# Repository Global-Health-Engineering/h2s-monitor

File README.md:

# H2S Monitor

Design and Development of a Low-Cost Hydrogen Sulfide Sensor System for Biogas Monitoring

**Author:** Flurin Vital
**Supervisors:** Prof. Dr. Elizabeth Tilley, Dr. Jakub Tkaczuk
**Institution:** ETH Zürich, Global Health Engineering (GHE)
**Date:** June 2026

## Overview

This project develops a low-cost, field-deployable hydrogen sulfide (H2S) sensor system for monitoring biogas quality. Biogas systems in low-resource settings frequently lack affordable tools for measuring H2S — a toxic and corrosive gas produced during anaerobic digestion that causes equipment degradation and safety hazards. Commercial H2S meters capable of covering the relevant concentration range (0–2000 ppm) cost upwards of CHF 4000 and are unsuitable for continuous field deployment.

The developed system integrates a three-electrode electrochemical H2S sensor into a single compact battery-powered device with a custom PCB, 3D-printed enclosure and gas flow chamber, and C++ firmware running on FreeRTOS. Total component cost is CHF 193.80 — approximately 95% cheaper than the commercial reference instrument (Dräger X-am 8000).

## System Components

| Component | Part |
|---|---|
| Microcontroller | Seeed XIAO ESP32-C6 |
| H2S Sensor | SUCH electrochemical, 0–2000 ppm, 85 ± 25 nA/ppm |
| Analog Front End | Texas Instruments LMP91002 |
| ADC | Texas Instruments ADS1115 (16-bit) |
| Display | 0.96" OLED, SSD1306 driver |
| RTC | Maxim DS3232M |
| Power Management | Texas Instruments BQ25185 |
| Storage | MicroSD card (SPI) |
| Gas Pump | DC micro diaphragm pump, 1.2 L/min |
| PCB | KiCad design, manufactured by JLCPCB |
| Enclosure | 3D-printed PLA (case) + resin (flow chamber) |

## Repository Structure

```
├── analysis/
├── data/
├── docs/
├── grading/
├── hardware/
├── media/
└── src/
```

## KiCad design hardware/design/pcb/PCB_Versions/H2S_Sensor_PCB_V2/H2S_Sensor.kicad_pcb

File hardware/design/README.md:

# Design

PCB schematic and layout files, and CAD models for the enclosure and gas flow chamber.

## Structure

```
design/
├── pcb/
└── case_CAD/
```

## PCB (`pcb/`)

Designed in KiCad. The schematic is organised into functional blocks:
- **Power management** — TI BQ25185 (USB-C charging, single-cell LiPo, power path)
- **Microcontroller** — Seeed XIAO ESP32-C6
- **Analog front end & ADC** — TI LMP91002 + TI ADS1115 for electrochemical sensor signal conditioning
- **Peripherals** — DS3232M RTC, SSD1306 OLED, MicroSD (SPI), pump MOSFET driver

Production files in `pcb/production/` and `pcb/jlcpcb/` were submitted to JLCPCB for fabrication and assembly. `pcb/PCB_Versions/` contains archived snapshots of earlier design iterations (V1–V5).

The electrochemical sensor uses a custom KiCad footprint with press-fit through-hole pads — the sensor cannot withstand soldering temperatures and must not be soldered.

## CAD (`case_CAD/`)

Designed in OnShape, exported as STL for 3D printing.

| File | Material | Notes |
|---|---|---|
| `Case/Final/Case_Bottom.stl` | PLA | Houses PCB |
| `Case/Final/Case_Top.stl` | PLA | Carries OLED display |
| `Flow_Chamber/Flow_Chamber_final.stl` | Resin (field) / PLA (bench test) | Seals around sensor body with O-ring |

`Case/V1`–`V5` and `Flow_Chamber/V1`–`V5` contain earlier design iterations.

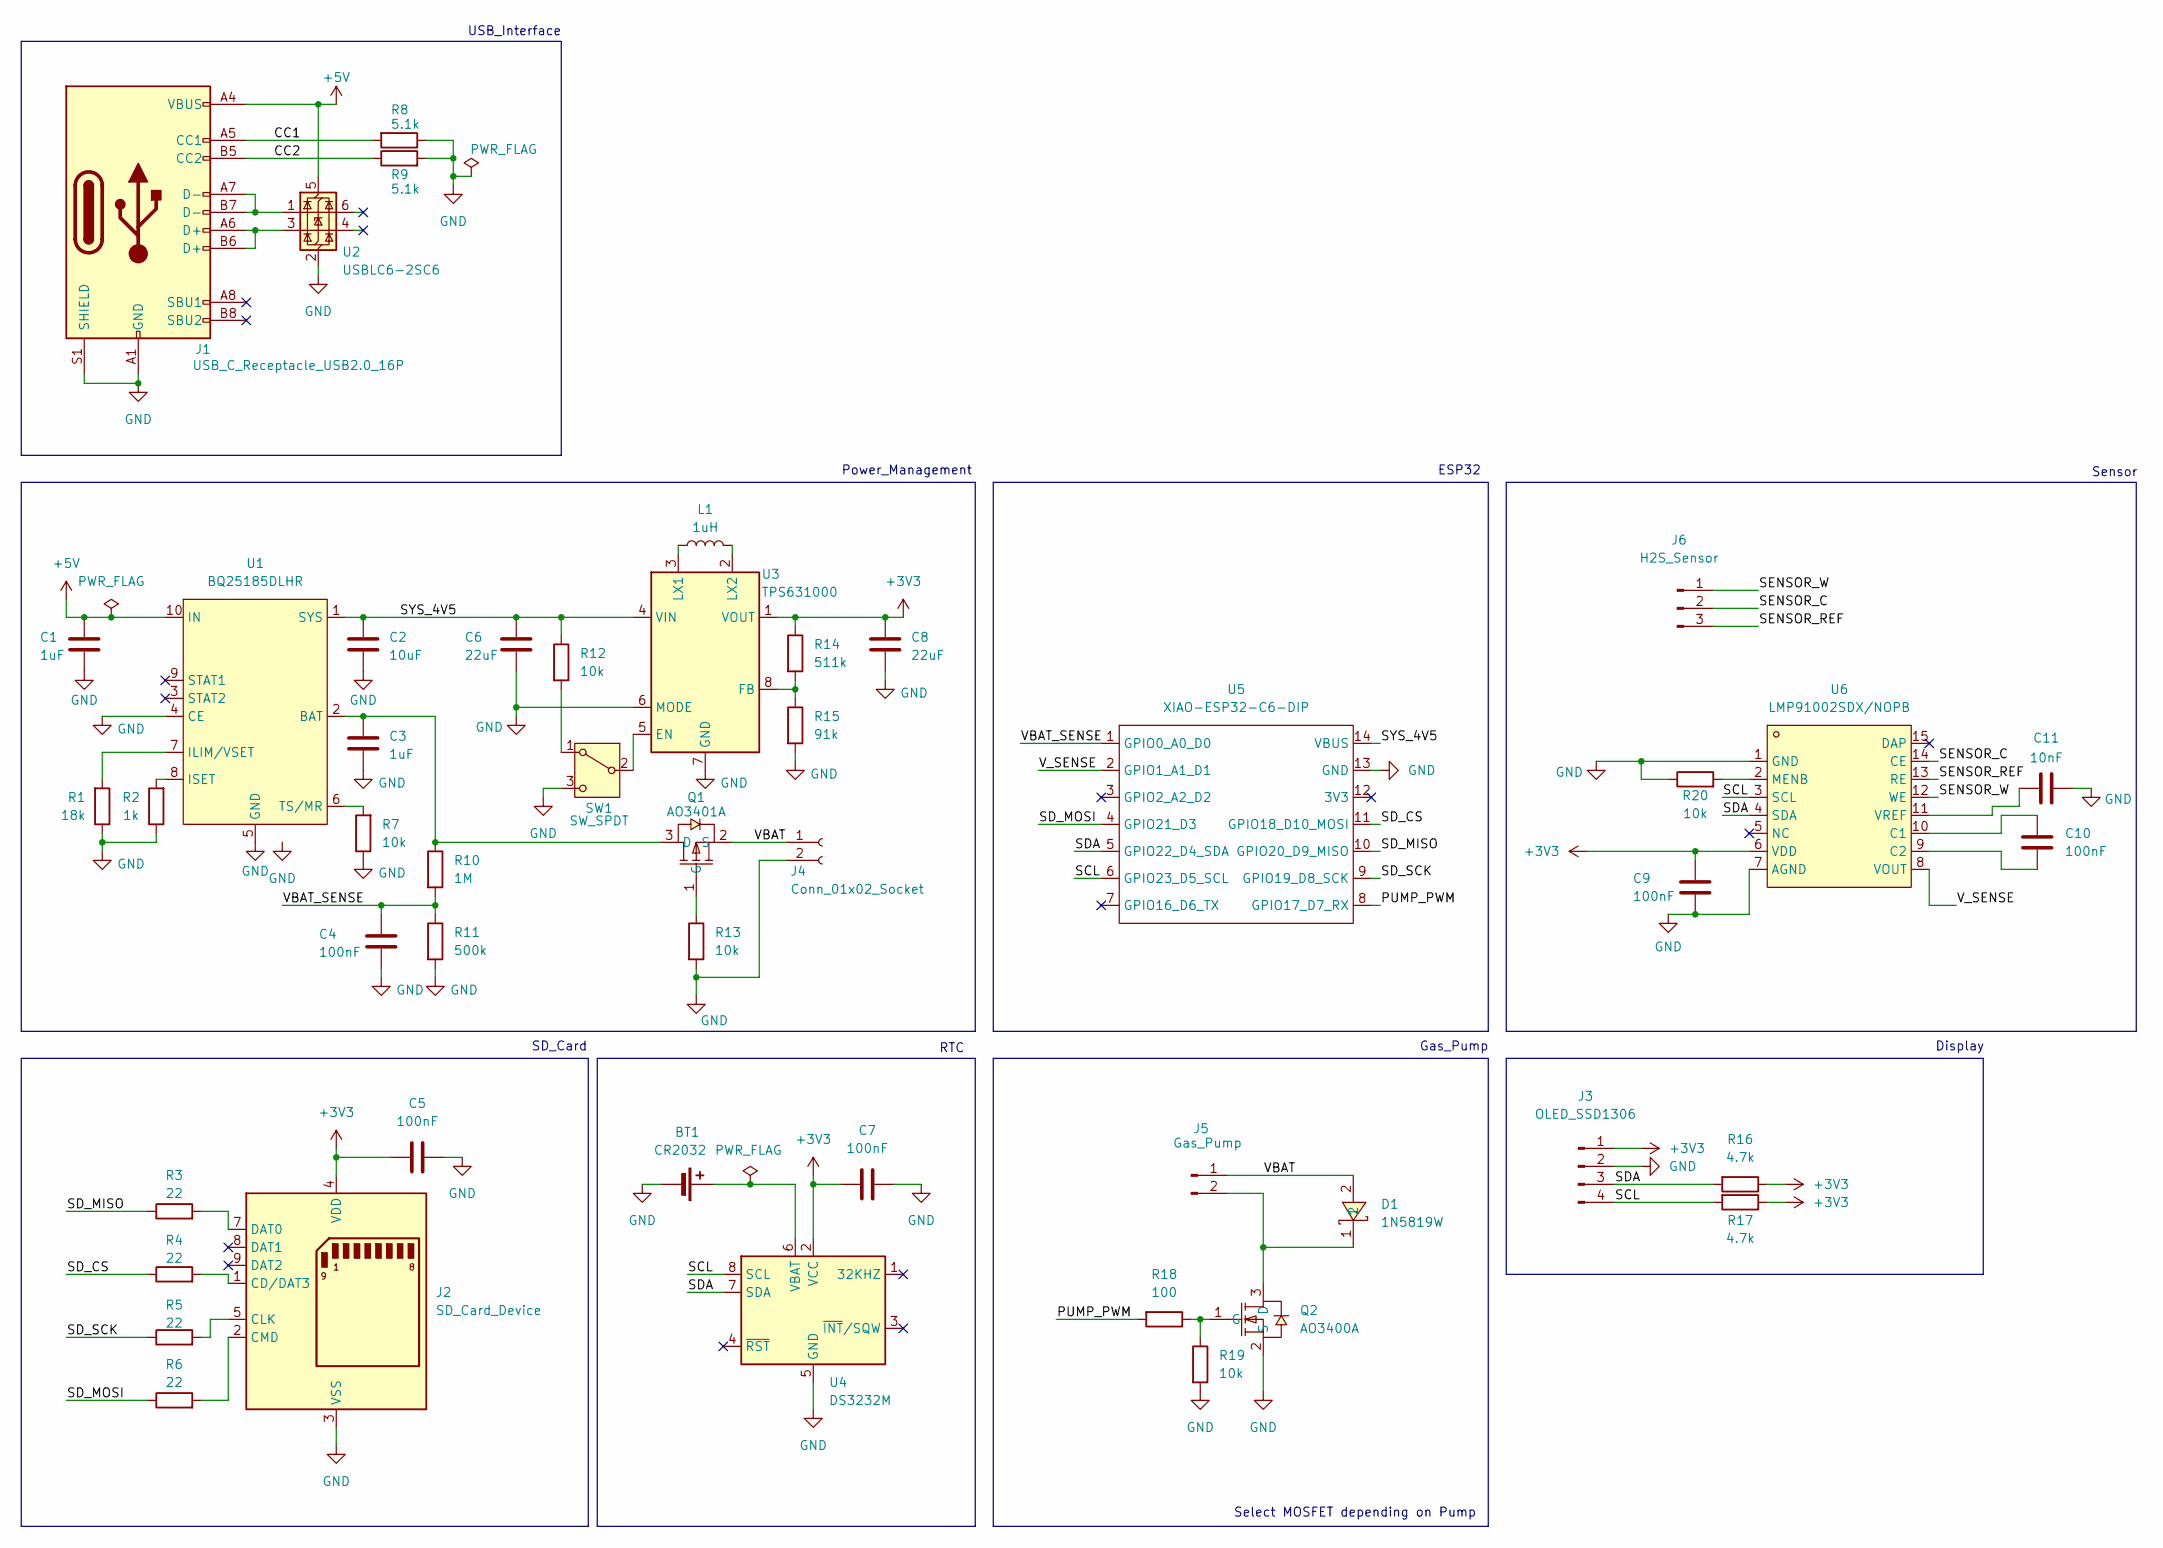
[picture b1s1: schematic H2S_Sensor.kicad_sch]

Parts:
BT1: CR2032; BAT-TH_CR2032-BS-6-1; LCSC Part C70377
C1, C3: 1uF; C_0603_1608Metric
C2: 10uF; C_0603_1608Metric
C4, C5, C7, C9, C10: 100nF; C_0603_1608Metric
C6, C8: 22uF; C_0603_1608Metric
C11: 10nF; C_0603_1608Metric
D1: 1N5819W; SOD-123F_L2.8-W1.8-LS3.7-RD; MPN 1N5819W; LCSC Part C169540
J1: USB_C_Receptacle_USB2.0_16P; USB_C_Receptacle_GCT_USB4105-xx-A_16P_TopMnt_Horizontal
J2: SD_Card_Device; SD-SMD_5045280892; LCSC Part C125620
J3: OLED_SSD1306; Hirose_DF13-04P-1.25DSA_1x04_P1.25mm_Vertical
J4: Conn_01x02_Socket; Hirose_DF13-02P-1.25DSA_1x02_P1.25mm_Vertical
J5: Gas_Pump; Hirose_DF13-02P-1.25DSA_1x02_P1.25mm_Vertical
J6: H2S_Sensor; H2S_Sensor_3Pin_D20mm
L1: 1uH; L_0805_2012Metric
Q1: AO3401A; SOT-23_L2.9-W1.3-P1.90-LS2.4-BR; MPN AO3401A; LCSC Part C15127
Q2: AO3400A; SOT-23-3_L2.9-W1.3-P1.90-LS2.4-BR; MPN AO3400A; LCSC Part C20917
R1: 18k; R_0603_1608Metric
R2: 1k; R_0603_1608Metric
R3, R4, R5, R6: 22; R_0603_1608Metric
R7, R12, R13, R19, R20: 10k; R_0603_1608Metric
R8, R9: 5.1k; R_0603_1608Metric
R10: 1M; R_0603_1608Metric
R11: 500k; R_0603_1608Metric
R14: 511k; R_0603_1608Metric
R15: 91k; R_0603_1608Metric
R16, R17: 4.7k; R_0603_1608Metric
R18: 100; R_0603_1608Metric
SW1: SW_SPDT; SW-SMD_MSK-03-HB; LCSC Part C54948
U1: BQ25185DLHR; WSON-10_L2.2-W2.0-P0.40-BL-EP_TI_DLH0010A; LCSC Part C19725033
U2: USBLC6-2SC6; SOT-23-6_L2.9-W1.6-P0.95-LS2.8-BL; LCSC Part C7519
U3: TPS631000; SOT-583-8_L2.1-W1.2-P0.50-LS1.6-BL; LCSC Part C5219190
U4: DS3232M; SOIC-8_3.9x4.9mm_P1.27mm
U5: XIAO-ESP32-C6-DIP
U6: LMP91002SDX/NOPB; WSON-14_L4.0-W4.0-P0.50-BL-EP; MPN LMP91002SDX/NOPB; LCSC Part C2651581

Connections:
+3V3: C5.1, C7.2, C8.2, C9.1, J2.4 (VDD), J3.1, R14.1, R16.1, R17.1, U3.1 (VOUT), U4.2 (VCC), U6.6 (VDD)
+5V: C1.2, J1.A4 (VBUS), J1.A9 (VBUS), J1.B4 (VBUS), J1.B9 (VBUS), U1.10 (IN), U2.5 (VBUS)
/CC1: J1.A5 (CC1), R8.2
/CC2: J1.B5 (CC2), R9.1
/PUMP_PWM: R18.2, U5.8 (GPIO17_D7_RX)
/SCL: J3.4, R17.2, U4.8 (SCL), U5.6 (GPIO23_D5_SCL), U6.3 (SCL)
/SDA: J3.3, R16.2, U4.7 (SDA), U5.5 (GPIO22_D4_SDA), U6.4 (SDA)
/SD_CS: R4.1, U5.11 (GPIO18_D10_MOSI)
/SD_MISO: R3.1, U5.10 (GPIO20_D9_MISO)
/SD_MOSI: R6.1, U5.4 (GPIO21_D3)
/SD_SCK: R5.1, U5.9 (GPIO19_D8_SCK)
/SENSOR_C: J6.2, U6.14 (CE)
/SENSOR_REF: J6.3, U6.13 (RE)
/SENSOR_W: J6.1, U6.12 (WE)
/SYS_4V5: C2.2, C6.2, R12.1, U1.1 (SYS), U3.4 (VIN), U5.14 (VBUS)
/VBAT: D1.2, J4.1, J5.1, Q1.2 (S)
/VBAT_SENSE: C4.1, R10.2, R11.1, U5.1 (GPIO0_A0_D0)
/V_SENSE: U5.2 (GPIO1_A1_D1), U6.8 (VOUT)
GND: BT1.2 (-), C1.1, C2.1, C3.1, C4.2, C5.2, C6.1, C7.1, C8.1, C9.2, C11.2, J1.A1 (GND), J1.A12 (GND), J1.B1 (GND), J1.B12 (GND), J1.S1 (SHIELD), J2.3 (VSS), J2.6 (VSS), J3.2, J4.2, Q2.2 (S), R1.1, R2.1, R7.1, R8.1, R9.2, R11.2, R13.2, R15.2, R19.2, R20.1, SW1.3 (C), U1.4 (CE), U1.5 (GND), U1.11 (VSS), U2.2 (GND), U3.6 (MODE), U3.7 (GND), U4.5 (GND), U5.13 (GND), U6.1 (GND), U6.7 (AGND), U6.15 (DAP)
unnamed: BT1.1 (+), U4.6 (VBAT)
unnamed: J1.A6 (D+), J1.B6 (D+), U2.3 (I/O2)
unnamed: J1.A7 (D-), J1.B7 (D-), U2.1 (I/O1)
unnamed: J2.1 (CD/DAT3), R4.2
unnamed: J2.5 (CLK), R5.2
unnamed: J2.2 (CMD), R6.2
unnamed: J2.7 (DAT0), R3.2
unnamed: D1.1, J5.2, Q2.3 (D)
unnamed: C3.2, Q1.3 (D), R10.1, U1.2 (BAT)
unnamed: Q1.1 (G), R13.1
unnamed: Q2.1 (G), R18.1, R19.1
unnamed: R12.2, SW1.1 (A)
unnamed: SW1.2 (B), U3.5 (EN)
unnamed: R1.2, U1.7 (ILIM/VSET)
unnamed: R2.2, U1.8 (ISET)
unnamed: R7.2, U1.6 (TS/MR)
unnamed: R14.2, R15.1, U3.8 (FB)
unnamed: L1.1, U3.3 (LX1)
unnamed: L1.2, U3.2 (LX2)
unnamed: C10.1, U6.10 (C1)
unnamed: C10.2, U6.9 (C2)
unnamed: R20.2, U6.2 (MENB)
unnamed: C11.1, U6.11 (VREF)

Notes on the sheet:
Gas_Pump
Sensor
USB_Interface
ESP32
Display
RTC
Select MOSFET depending on Pump
SD_Card
Power_Management

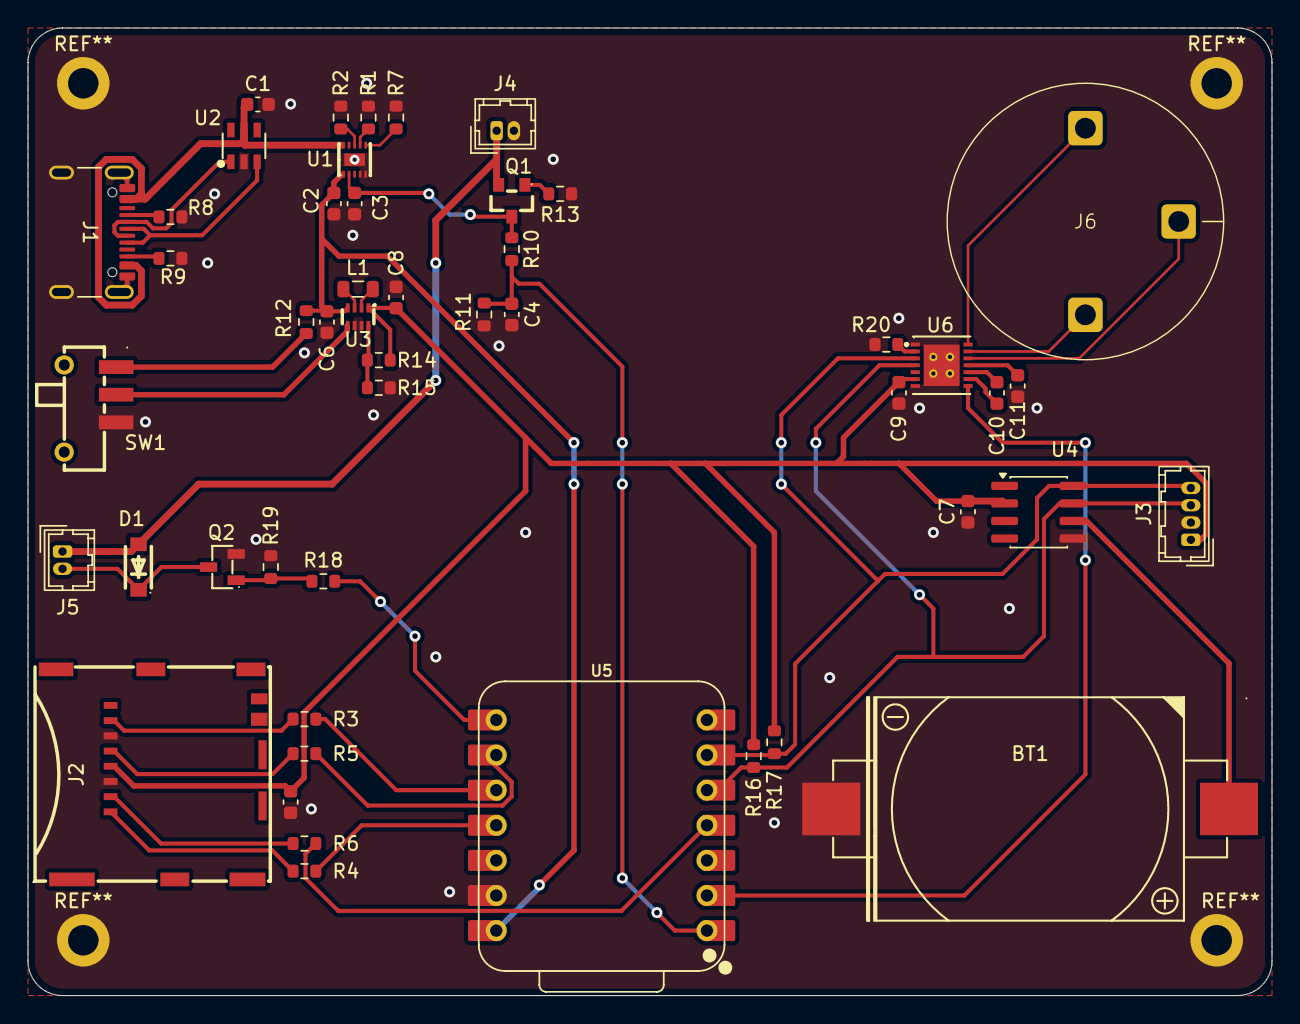
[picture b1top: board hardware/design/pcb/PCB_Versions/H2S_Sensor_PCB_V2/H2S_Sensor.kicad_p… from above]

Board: 2 copper layers, 90.0 x 70.0 mm, 49 parts (0 on the bottom side), 42 nets.

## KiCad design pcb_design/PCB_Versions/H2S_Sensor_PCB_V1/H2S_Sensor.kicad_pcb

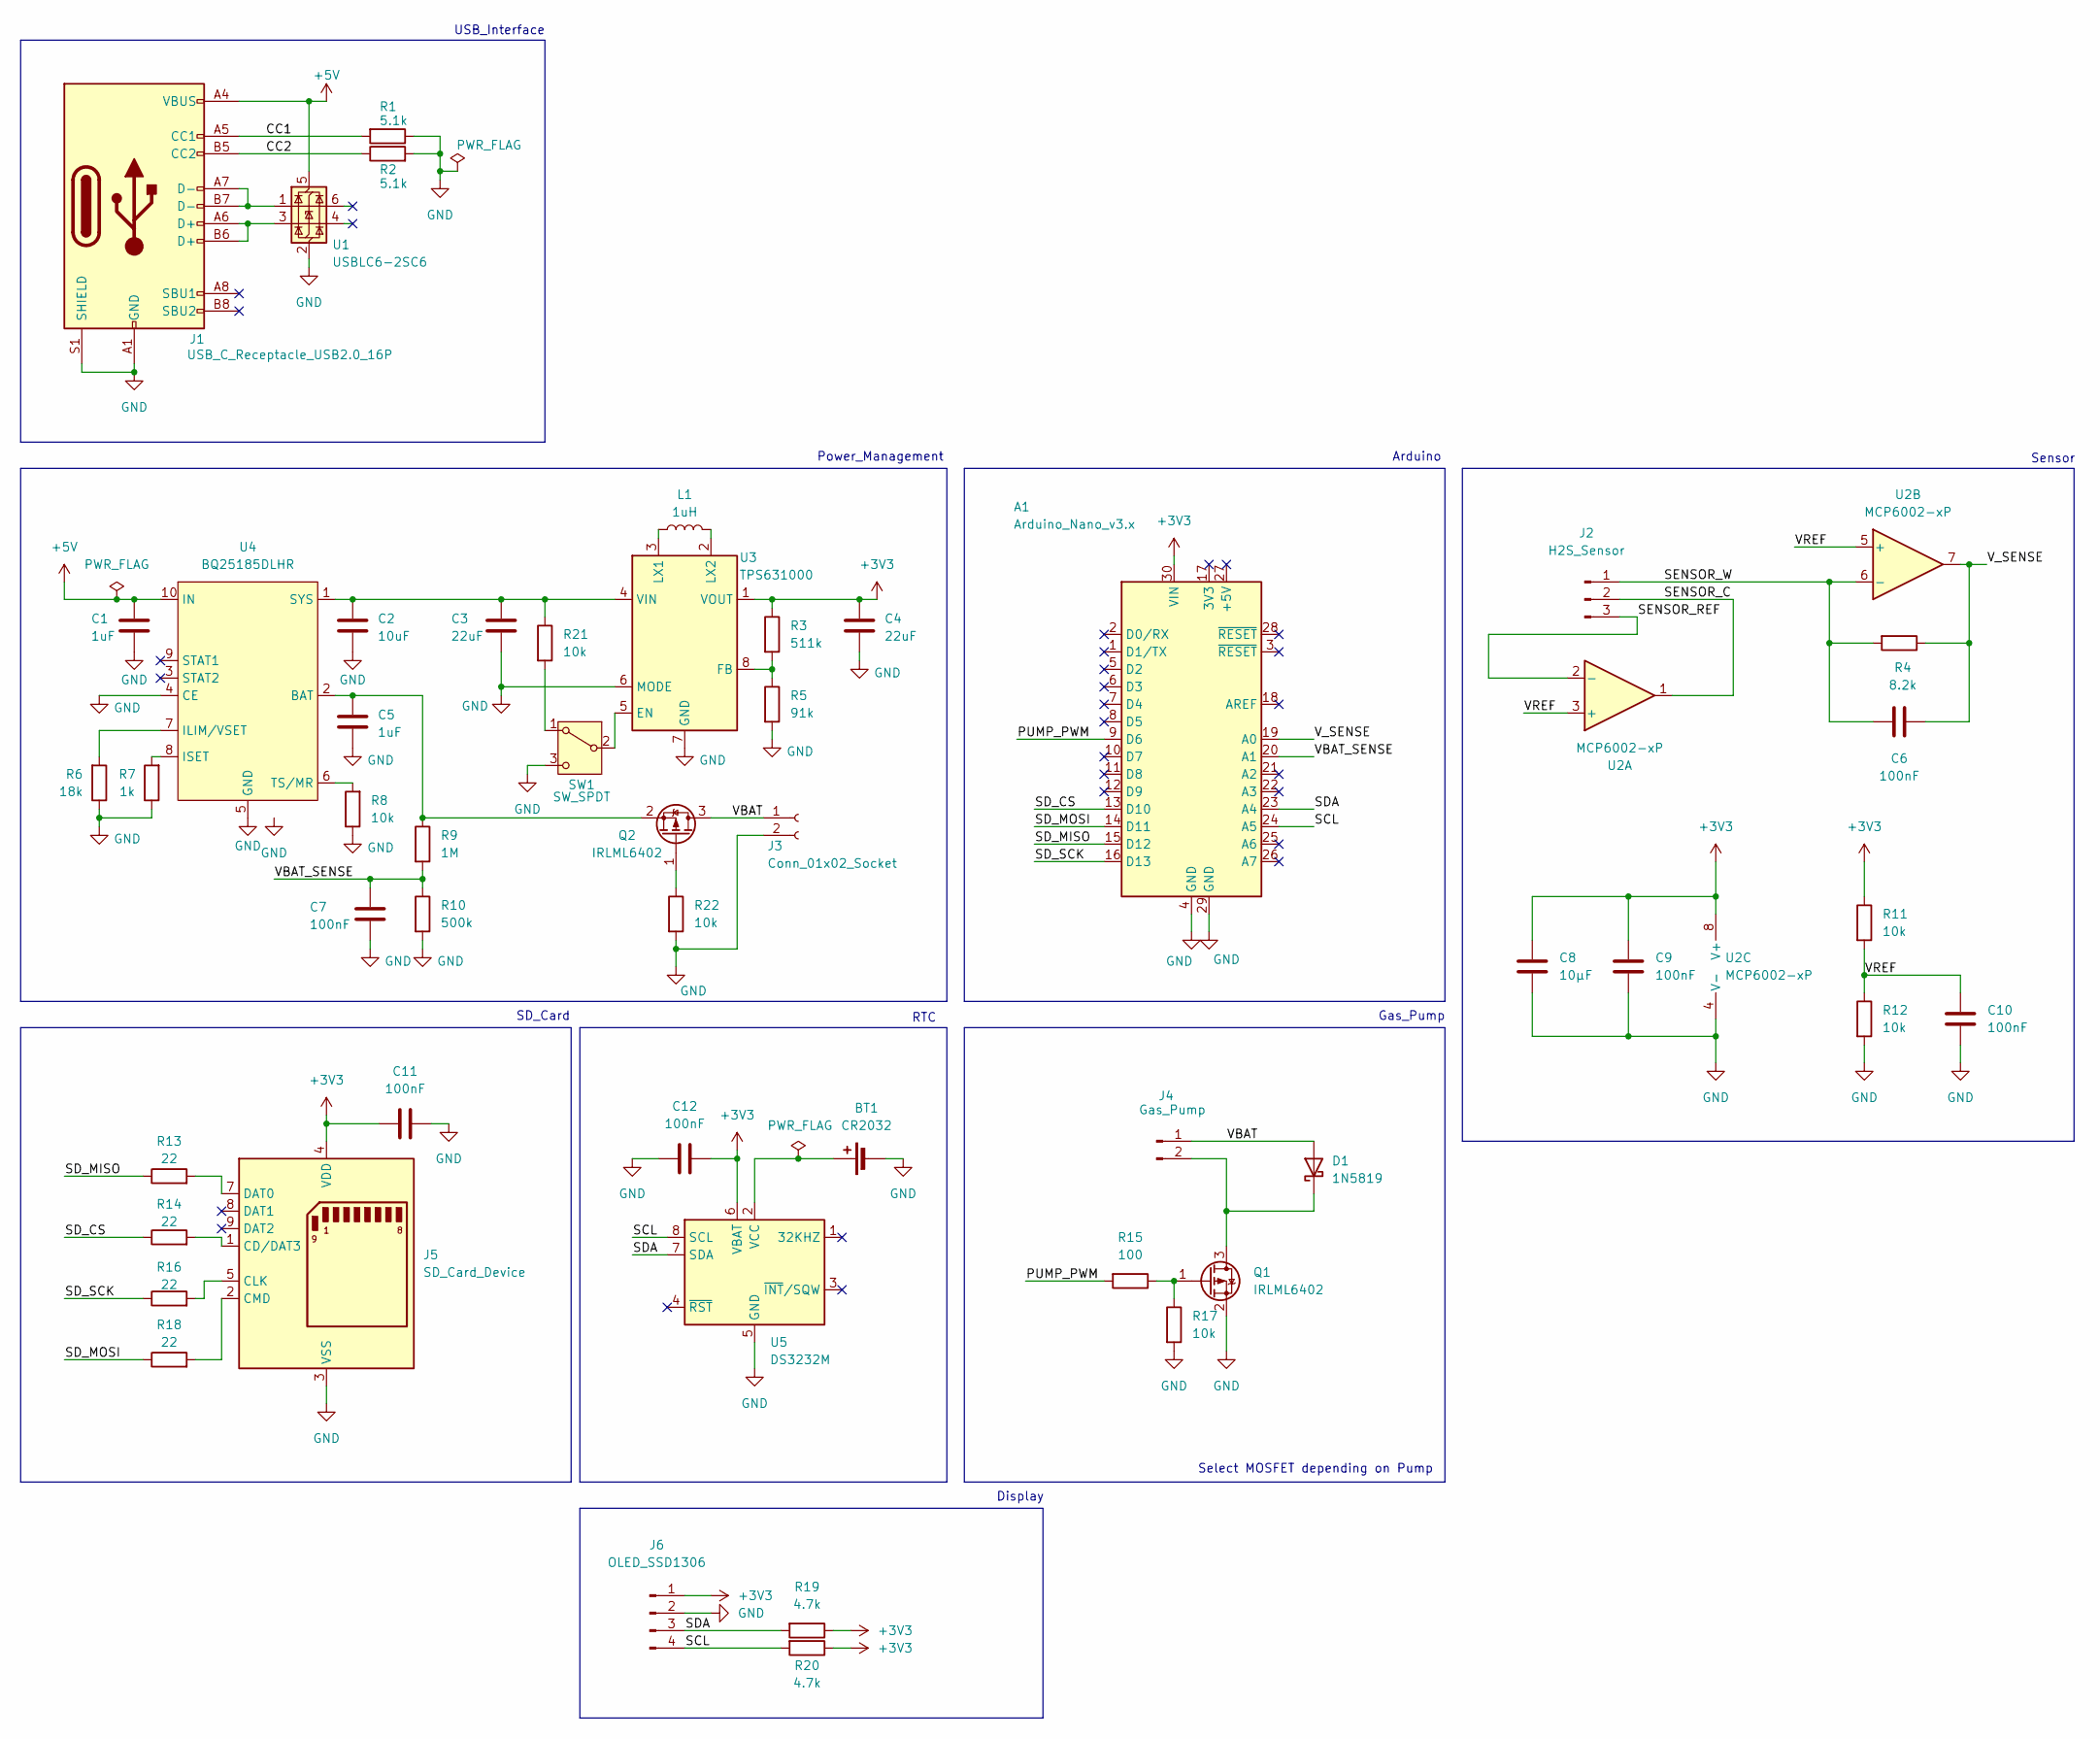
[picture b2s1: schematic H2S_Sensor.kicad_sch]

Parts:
A1: Arduino_Nano_v3.x; Arduino_Nano
BT1: CR2032; BAT-TH_CR2032-BS-6-1; LCSC Part C70377
C1, C5: 1uF; C_0603_1608Metric
C2: 10uF; C_0603_1608Metric
C3, C4: 22uF; C_0603_1608Metric
C6, C7, C9, C10, C11, C12: 100nF; C_0603_1608Metric
C8: 10µF; C_0603_1608Metric
D1: 1N5819; DO-41_BD2.4-L4.7-P8.70-D0.9-FD; LCSC Part C2474
J1: USB_C_Receptacle_USB2.0_16P; USB_C_Receptacle_GCT_USB4105-xx-A_16P_TopMnt_Horizontal
J2: H2S_Sensor; H2S_Sensor_3Pin_D20mm
J3: Conn_01x02_Socket; Hirose_DF13-02P-1.25DSA_1x02_P1.25mm_Vertical
J4: Gas_Pump; Hirose_DF13-02P-1.25DSA_1x02_P1.25mm_Vertical
J5: SD_Card_Device; SD-SMD_SD-006S-T; LCSC Part C125620
J6: OLED_SSD1306; Hirose_DF13-04P-1.25DSA_1x04_P1.25mm_Vertical
L1: 1uH; L_0805_2012Metric
Q1, Q2: IRLML6402; SOT-23
R1, R2: 5.1k; R_0603_1608Metric
R3: 511k; R_0603_1608Metric
R4: 8.2k; R_0603_1608Metric
R5: 91k; R_0603_1608Metric
R6: 18k; R_0603_1608Metric
R7: 1k; R_0603_1608Metric
R8, R11, R12, R17, R21, R22: 10k; R_0603_1608Metric
R9: 1M; R_0603_1608Metric
R10: 500k; R_0603_1608Metric
R13, R14, R16, R18: 22; R_0603_1608Metric
R15: 100; R_0603_1608Metric
R19, R20: 4.7k; R_0603_1608Metric
SW1: SW_SPDT; SW-SMD_MSK-03-HB; LCSC Part C54948
U1: USBLC6-2SC6; SOT-23-6_L2.9-W1.6-P0.95-LS2.8-BL; LCSC Part C7519
U2: MCP6002-xP; SOIC-8_3.9x4.9mm_P1.27mm
U3: TPS631000; SOT-583-8_L2.1-W1.2-P0.50-LS1.6-BL; LCSC Part C5219190
U4: BQ25185DLHR; WSON-10_L2.2-W2.0-P0.40-BL-EP_TI_DLH0010A; LCSC Part C19725033
U5: DS3232M; SOIC-8_3.9x4.9mm_P1.27mm

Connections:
+3V3: A1.30 (VIN), C4.2, C8.1, C9.1, C11.1, C12.2, J5.4 (VDD), J6.1, R3.1, R11.1, R19.1, R20.1, U2.8 (V+), U3.1 (VOUT), U5.6 (VBAT)
+5V: C1.2, J1.A4 (VBUS), J1.A9 (VBUS), J1.B4 (VBUS), J1.B9 (VBUS), U1.5 (VBUS), U4.10 (IN)
/CC1: J1.A5 (CC1), R1.2
/CC2: J1.B5 (CC2), R2.1
/PUMP_PWM: A1.9 (D6), R15.2
/SCL: A1.24 (A5), J6.4, R20.2, U5.8 (SCL)
/SDA: A1.23 (A4), J6.3, R19.2, U5.7 (SDA)
/SD_CS: A1.13 (D10), R14.1
/SD_MISO: A1.15 (D12), R13.1
/SD_MOSI: A1.14 (D11), R18.1
/SD_SCK: A1.16 (D13), R16.1
/SENSOR_C: J2.2, U2.1
/SENSOR_REF: J2.3, U2.2 (-)
/SENSOR_W: C6.1, J2.1, R4.2, U2.6 (-)
/VBAT: D1.2 (A), J3.1, J4.1, Q2.3 (D)
/VBAT_SENSE: A1.20 (A1), C7.1, R9.2, R10.1
/VREF: C10.1, R11.2, R12.1, U2.3 (+), U2.5 (+)
/V_SENSE: A1.19 (A0), C6.2, R4.1, U2.7
GND: A1.4 (GND), A1.29 (GND), BT1.2 (-), C1.1, C2.1, C3.1, C4.1, C5.1, C7.2, C8.2, C9.2, C10.2, C11.2, C12.1, J1.A1 (GND), J1.A12 (GND), J1.B1 (GND), J1.B12 (GND), J1.S1 (SHIELD), J3.2, J5.3 (VSS), J5.6 (VSS), J6.2, Q1.2 (S), R1.1, R2.2, R5.2, R6.1, R7.1, R8.1, R10.2, R12.2, R17.2, R22.2, SW1.3 (C), U1.2 (GND), U2.4 (V-), U3.6 (MODE), U3.7 (GND), U4.4 (CE), U4.5 (GND), U4.11 (VSS), U5.5 (GND)
unnamed: BT1.1 (+), U5.2 (VCC)
unnamed: D1.1 (K), J4.2, Q1.3 (D)
unnamed: J1.A6 (D+), J1.B6 (D+), U1.3 (I/O2)
unnamed: J1.A7 (D-), J1.B7 (D-), U1.1 (I/O1)
unnamed: J5.1 (CD/DAT3), R14.2
unnamed: J5.5 (CLK), R16.2
unnamed: J5.2 (CMD), R18.2
unnamed: J5.7 (DAT0), R13.2
unnamed: Q1.1 (G), R15.1, R17.1
unnamed: Q2.1 (G), R22.1
unnamed: C5.2, Q2.2 (S), R9.1, U4.2 (BAT)
unnamed: R21.2, SW1.1 (A)
unnamed: SW1.2 (B), U3.5 (EN)
unnamed: R3.2, R5.1, U3.8 (FB)
unnamed: L1.1, U3.3 (LX1)
unnamed: L1.2, U3.2 (LX2)
unnamed: C2.2, C3.2, R21.1, U3.4 (VIN), U4.1 (SYS)
unnamed: R6.2, U4.7 (ILIM/VSET)
unnamed: R7.2, U4.8 (ISET)
unnamed: R8.2, U4.6 (TS/MR)

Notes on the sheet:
Gas_Pump
Sensor
USB_Interface
Arduino
Display
RTC
Select MOSFET depending on Pump
SD_Card
Power_Management

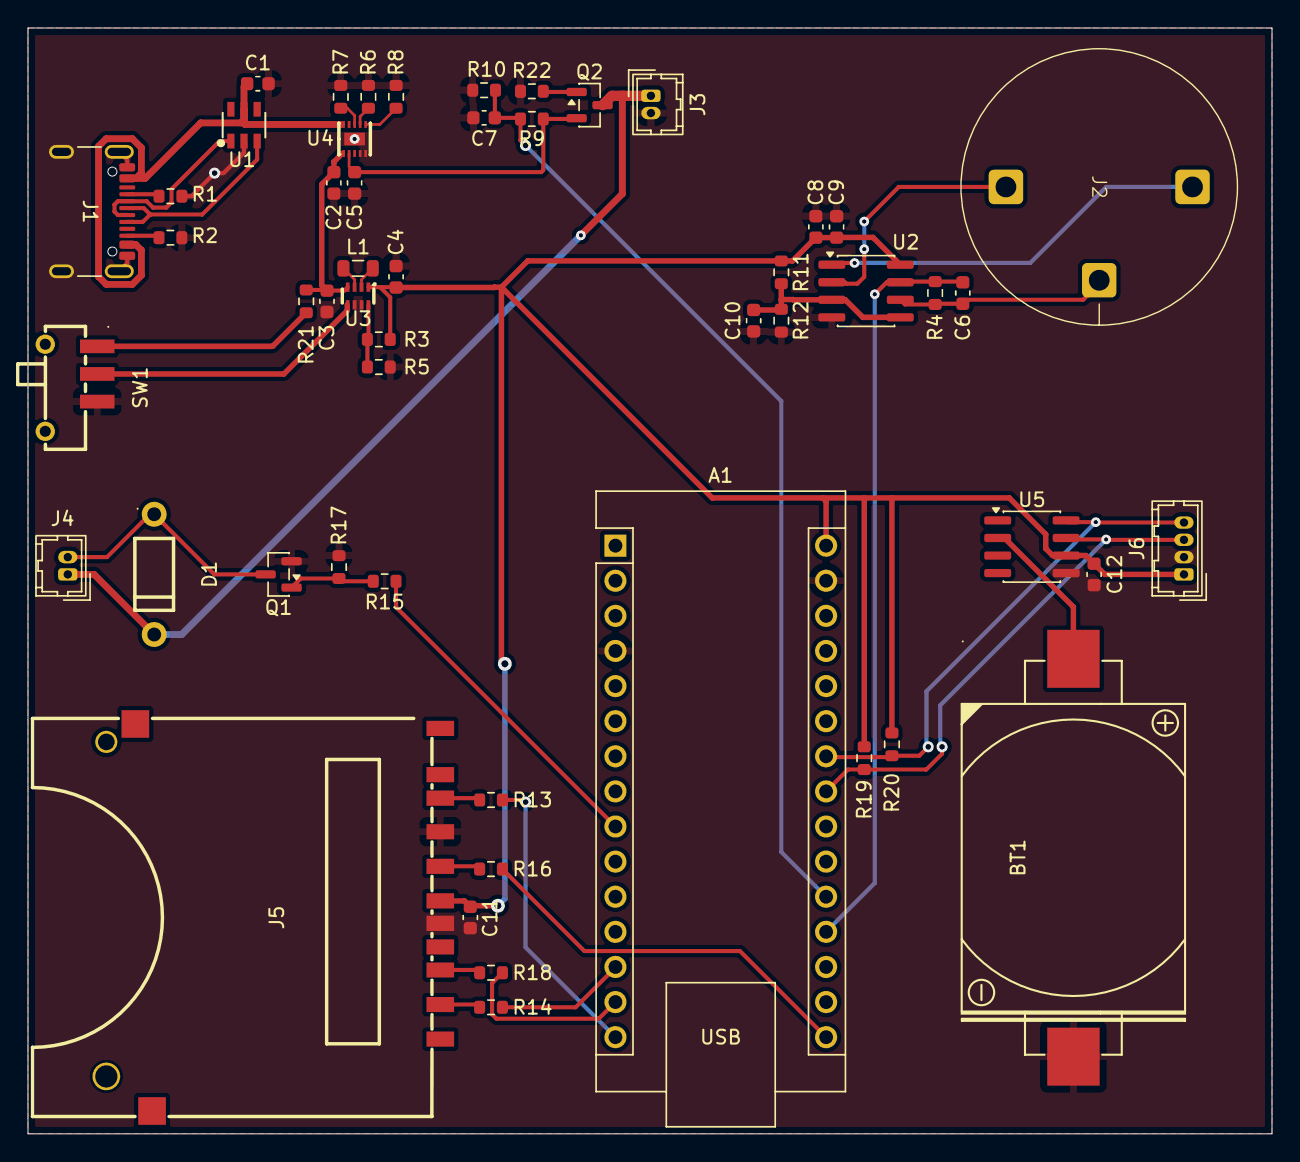
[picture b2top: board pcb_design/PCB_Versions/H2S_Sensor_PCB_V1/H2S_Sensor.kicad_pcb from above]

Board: 2 copper layers, 90.0 x 80.0 mm, 52 parts (0 on the bottom side), 39 nets.

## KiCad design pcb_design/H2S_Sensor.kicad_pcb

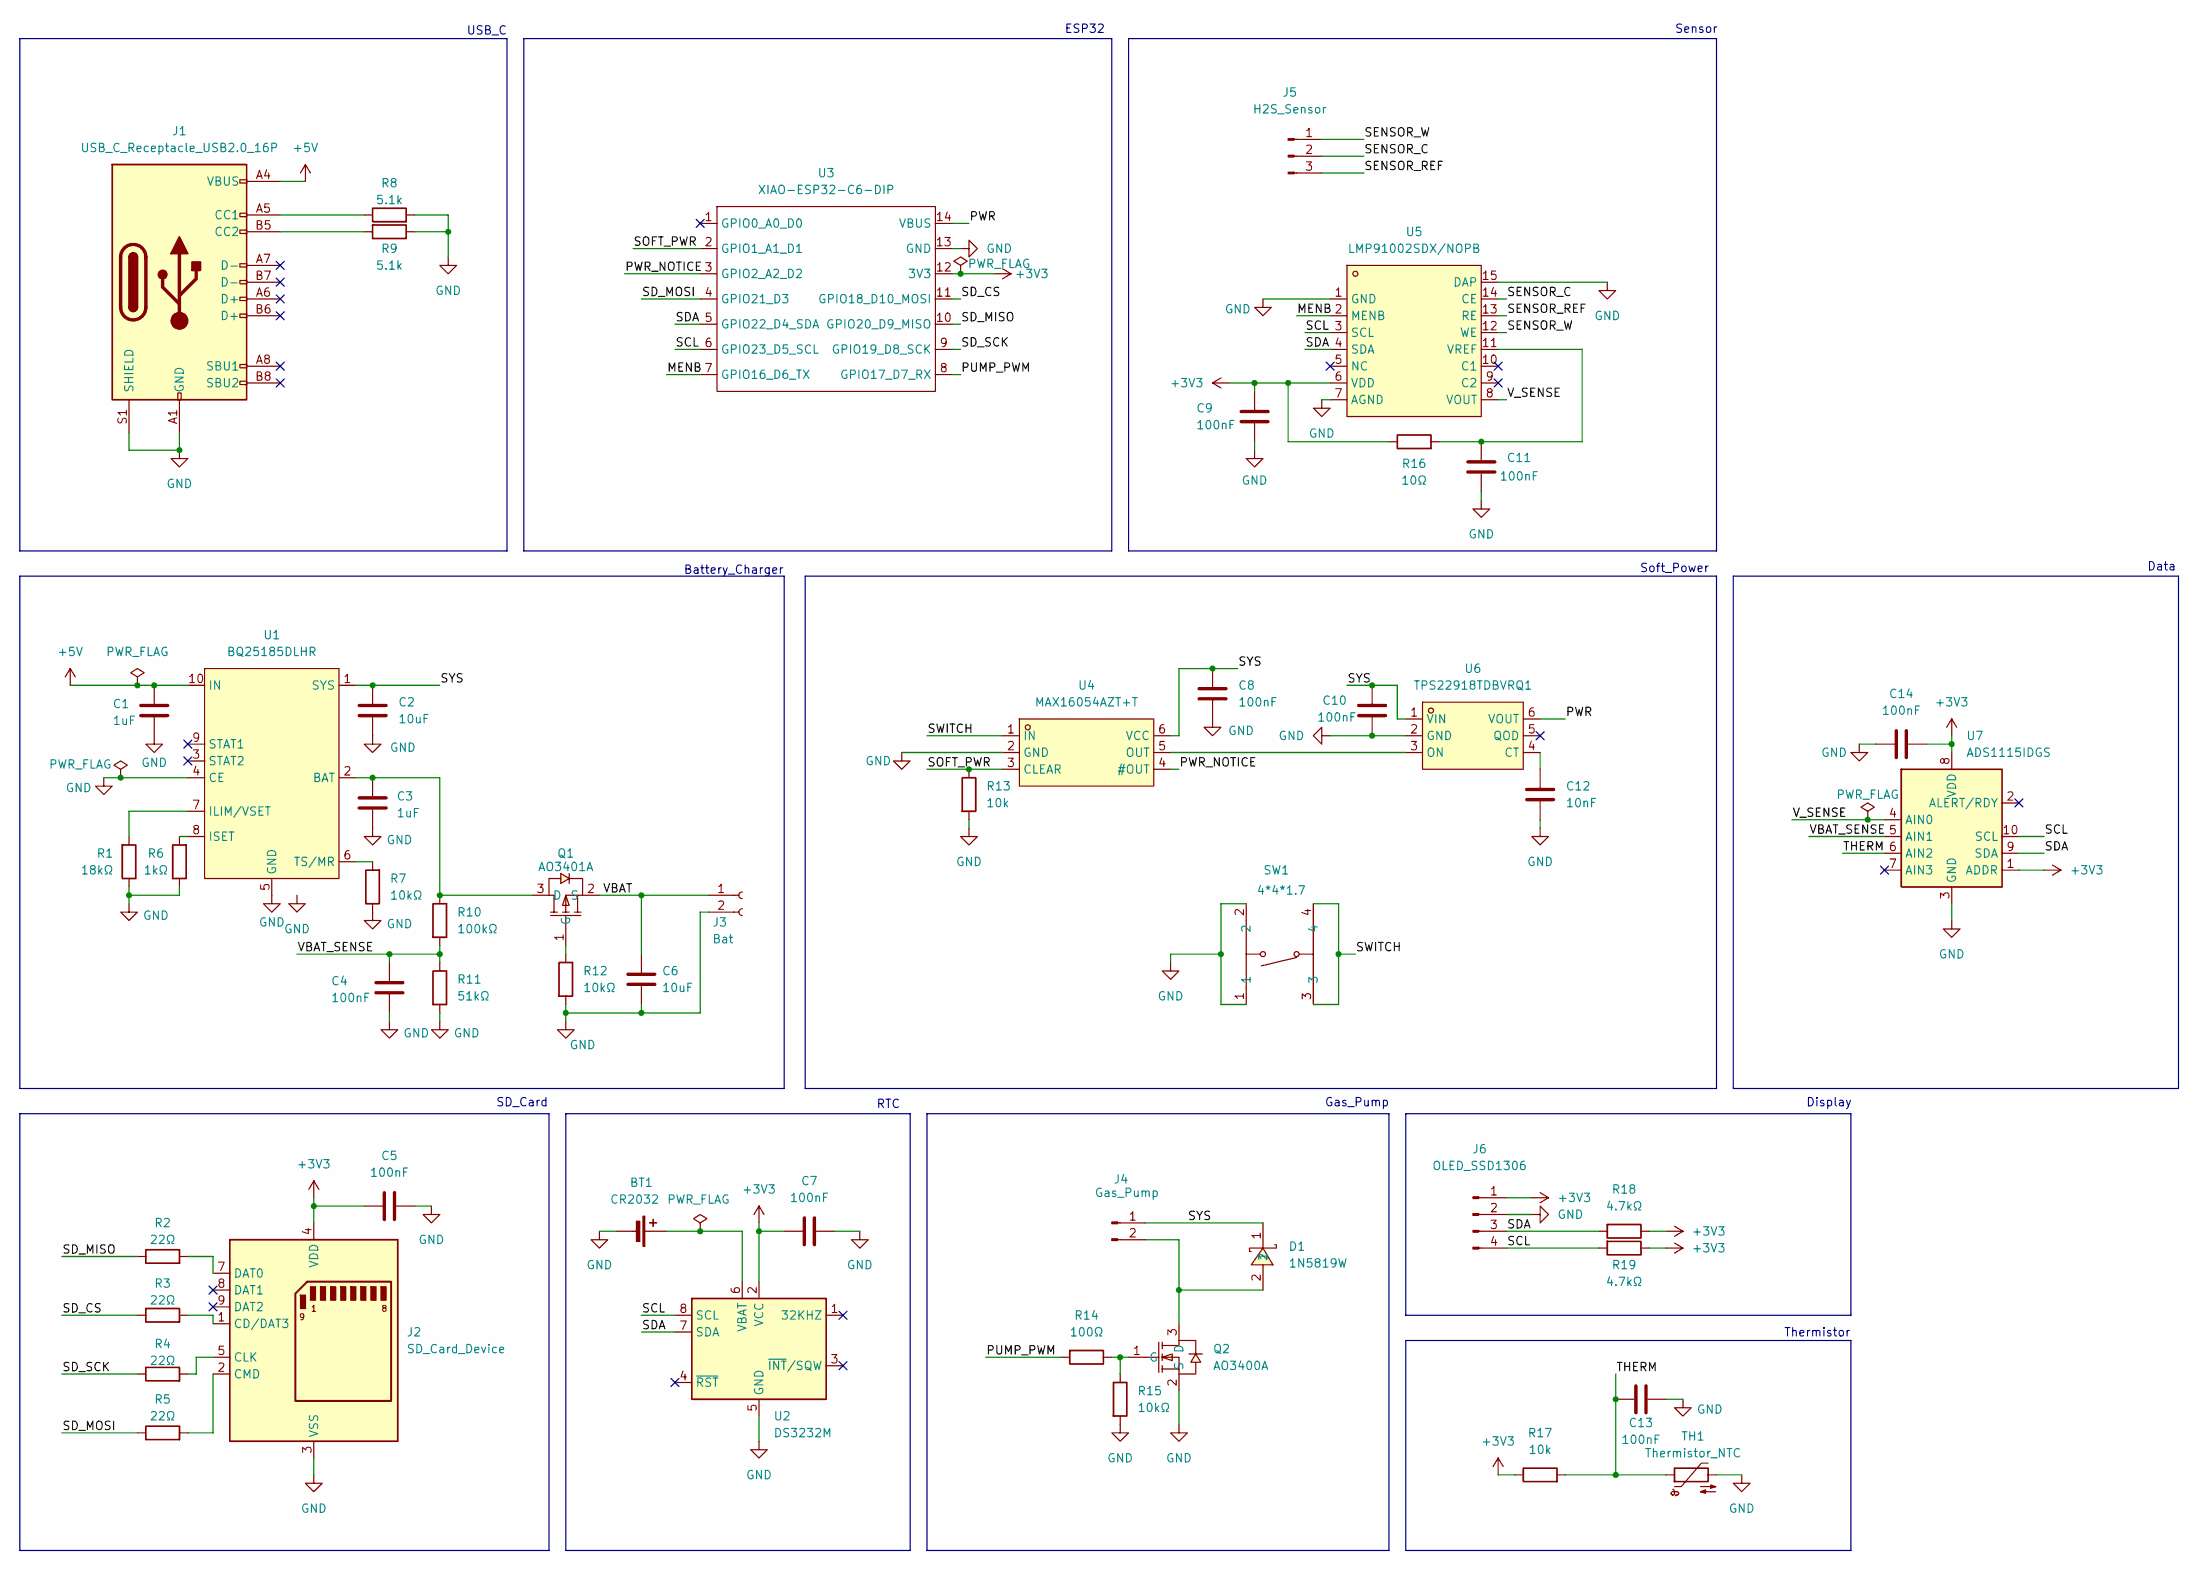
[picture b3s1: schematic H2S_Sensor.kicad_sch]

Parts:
BT1: CR2032; BAT-TH_CR2032-BS-6-1; LCSC Part C70377
C1, C3: 1uF; C_0603_1608Metric; LCSC Part C15849
C2, C6: 10uF; C_0603_1608Metric; LCSC Part C96446
C4, C5, C7, C8, C9, C10, C11, C13, C14: 100nF; C_0603_1608Metric; LCSC Part C14663
C12: 10nF; C_0603_1608Metric; LCSC Part C57112
D1: 1N5819W; SOD-123F_L2.8-W1.8-LS3.7-RD; MPN 1N5819W; LCSC Part C169540
J1: USB_C_Receptacle_USB2.0_16P; USB_C_Receptacle_GCT_USB4105-xx-A_16P_TopMnt_Horizontal; LCSC Part C2927037
J2: SD_Card_Device; TF-SMD_TF-15-15; LCSC Part C111196
J3: Bat; PinSocket_1x02_P2.54mm_Vertical
J4: Gas_Pump; PinSocket_1x02_P2.54mm_Vertical
J5: H2S_Sensor; H2S_Sensor_3Pin_D20mm
J6: OLED_SSD1306; PinSocket_1x04_P2.54mm_Vertical
Q1: AO3401A; SOT-23_L2.9-W1.3-P1.90-LS2.4-BR; MPN AO3401A; LCSC Part C15127
Q2: AO3400A; SOT-23-3_L2.9-W1.3-P1.90-LS2.4-BR; MPN AO3400A; LCSC Part C20917
R1: 18kΩ; R_0603_1608Metric; LCSC Part C25810
R2, R3, R4, R5: 22Ω; R_0603_1608Metric; LCSC Part C23345
R6: 1kΩ; R_0603_1608Metric; LCSC Part C21190
R7, R12, R15: 10kΩ; R_0603_1608Metric; LCSC Part C25804
R8, R9: 5.1k; R_0603_1608Metric; LCSC Part C23186
R10: 100kΩ; R_0603_1608Metric; LCSC Part C22935
R11: 51kΩ; R_0603_1608Metric; LCSC Part C23192
R13, R17: 10k; R_0603_1608Metric; LCSC Part C25804
R14: 100Ω; R_0603_1608Metric; LCSC Part C22775
R16: 10Ω; R_0603_1608Metric; LCSC Part C22859
R18, R19: 4.7kΩ; R_0603_1608Metric; LCSC Part C23162
SW1: 4*4*1.7; SW-SMD_4P-L5.2-W5.2-P3.70-LS6.5; MPN 4*4*1.7 贴片; LCSC Part C10852
TH1: Thermistor_NTC; R_0603_1608Metric; LCSC Part C7462093
U1: BQ25185DLHR; WSON-10_L2.2-W2.0-P0.40-BL-EP_TI_DLH0010A; LCSC C19725033
U2: DS3232M; SOIC-8_3.9x4.9mm_P1.27mm; LCSC Part C2827535
U3: XIAO-ESP32-C6-DIP
U4: MAX16054AZT+T; TSOT-23-6_L2.9-W1.6-P0.95-LS2.8-TL; MPN MAX16054AZT+T; LCSC Part C79401
U5: LMP91002SDX/NOPB; WSON-14_L4.0-W4.0-P0.50-BL-EP; MPN LMP91002SDX/NOPB; LCSC Part C2651581
U6: TPS22918TDBVRQ1; SOT-23-6_L2.9-W1.6-P0.95-LS2.8-BR; MPN TPS22918TDBVRQ1; LCSC Part C2653760
U7: ADS1115IDGS; TSSOP-10_3x3mm_P0.5mm; LCSC Part C468683

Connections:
+3V3: C5.1, C7.2, C9.1, C14.2, J2.4 (VDD), J6.1, R16.1, R17.1, R18.1, R19.1, U2.2 (VCC), U3.12 (3V3), U5.6 (VDD), U7.1 (ADDR), U7.8 (VDD)
+5V: C1.2, J1.A4 (VBUS), J1.A9 (VBUS), J1.B4 (VBUS), J1.B9 (VBUS), U1.10 (IN)
/MENB: U3.7 (GPIO16_D6_TX), U5.2 (MENB)
/PUMP_PWM: R14.2, U3.8 (GPIO17_D7_RX)
/PWR: U3.14 (VBUS), U6.6 (VOUT)
/PWR_NOTICE: U3.3 (GPIO2_A2_D2), U4.4 (#OUT)
/SCL: J6.4, R19.2, U2.8 (SCL), U3.6 (GPIO23_D5_SCL), U5.3 (SCL), U7.10 (SCL)
/SDA: J6.3, R18.2, U2.7 (SDA), U3.5 (GPIO22_D4_SDA), U5.4 (SDA), U7.9 (SDA)
/SD_CS: R3.1, U3.11 (GPIO18_D10_MOSI)
/SD_MISO: R2.1, U3.10 (GPIO20_D9_MISO)
/SD_MOSI: R5.1, U3.4 (GPIO21_D3)
/SD_SCK: R4.1, U3.9 (GPIO19_D8_SCK)
/SENSOR_C: J5.2, U5.14 (CE)
/SENSOR_REF: J5.3, U5.13 (RE)
/SENSOR_W: J5.1, U5.12 (WE)
/SOFT_PWR: R13.1, U3.2 (GPIO1_A1_D1), U4.3 (CLEAR)
/SWITCH: SW1.3, SW1.4, U4.1 (IN)
/SYS: C2.1, C8.1, C10.1, D1.1, J4.1, U1.1 (SYS), U4.6 (VCC), U6.1 (VIN)
/THERM: C13.2, R17.2, TH1.1, U7.6 (AIN2)
/VBAT: C6.2, J3.1, Q1.2 (S)
/VBAT_SENSE: C4.1, R10.2, R11.1, U7.5 (AIN1)
/V_SENSE: U5.8 (VOUT), U7.4 (AIN0)
GND: BT1.2 (-), C1.1, C2.2, C3.1, C4.2, C5.2, C6.1, C7.1, C8.2, C9.2, C10.2, C11.2, C12.2, C13.1, C14.1, J1.A1 (GND), J1.A12 (GND), J1.B1 (GND), J1.B12 (GND), J1.S1 (SHIELD), J2.3 (VSS), J2.6 (VSS), J3.2, J6.2, Q2.2 (S), R1.1, R6.1, R7.1, R8.2, R9.1, R11.2, R12.2, R13.2, R15.2, SW1.1, SW1.2, TH1.2, U1.4 (CE), U1.5 (GND), U1.11 (VSS), U2.5 (GND), U3.13 (GND), U4.2 (GND), U5.1 (GND), U5.7 (AGND), U5.15 (DAP), U6.2 (GND), U7.3 (GND)
unnamed: BT1.1 (+), U2.6 (VBAT)
unnamed: J1.A5 (CC1), R8.1
unnamed: J1.B5 (CC2), R9.2
unnamed: J2.1 (CD/DAT3), R3.2
unnamed: J2.5 (CLK), R4.2
unnamed: J2.2 (CMD), R5.2
unnamed: J2.7 (DAT0), R2.2
unnamed: D1.2, J4.2, Q2.3 (D)
unnamed: C3.2, Q1.3 (D), R10.1, U1.2 (BAT)
unnamed: Q1.1 (G), R12.1
unnamed: Q2.1 (G), R14.1, R15.1
unnamed: R1.2, U1.7 (ILIM/VSET)
unnamed: R6.2, U1.8 (ISET)
unnamed: R7.2, U1.6 (TS/MR)
unnamed: U4.5 (OUT), U6.3 (ON)
unnamed: C11.1, R16.2, U5.11 (VREF)
unnamed: C12.1, U6.4 (CT)

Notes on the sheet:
Gas_Pump
Sensor
Thermistor
ESP32
Display
RTC
Data
Soft_Power
SD_Card
USB_C
Battery_Charger

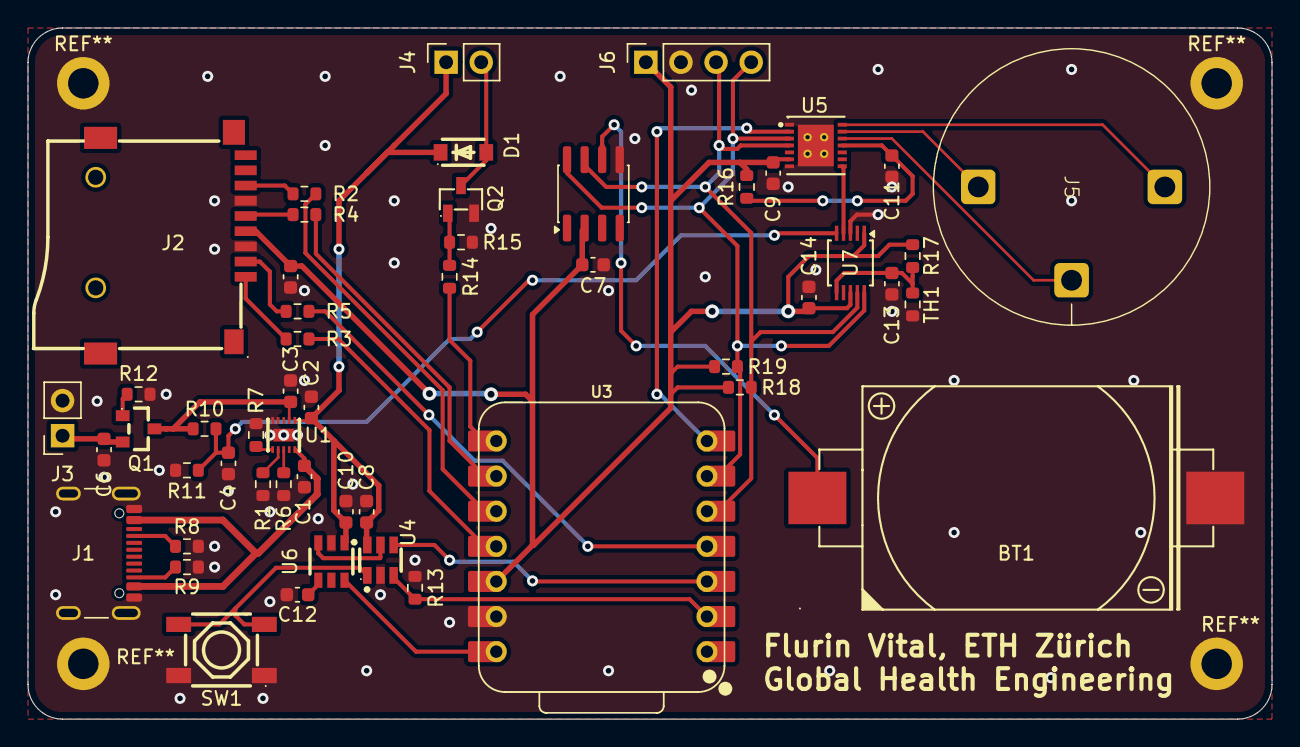
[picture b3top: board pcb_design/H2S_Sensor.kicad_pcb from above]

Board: 2 copper layers, 90.0 x 50.0 mm, 52 parts (0 on the bottom side), 40 nets.
